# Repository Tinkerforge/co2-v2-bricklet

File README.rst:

CO2 Bricklet 2.0
================

This repository contains the firmware source code and the hardware design
files. The documentation generator configs can be found at
https://github.com/Tinkerforge/generators

Repository Content
------------------

software/:
 * examples/: Examples for all supported languages
 * build/: Compiled files
 * src/: Source code of firmware
 * Makefile: Makefile to build project

hardware/:
 * Contains KiCad project files and additionally schematics as PDF

datasheets/:
 * Contains datasheets for sensors and complex ICs that are used

Hardware
--------

The hardware is designed with the open source EDA Suite KiCad
(http://www.kicad.org). Before you are able to open the files,
you have to install the Tinkerforge kicad-libraries
(https://github.com/Tinkerforge/kicad-libraries). You can either clone
them directly in hardware/ or clone them in a separate folder and
symlink them into hardware/
(ln -s kicad_path/kicad-libraries project_path/hardware). After that you
can open the .pro file in hardware/ with KiCad and from there view and
modify the schematics and the PCB layout.

Software
--------

If you want to do your own Brick/Bricklet firmware development we highly
recommend that you use our build environment setup script and read the
tutorial (https://www.tinkerforge.com/en/doc/Tutorials/Tutorial_Build_Environment/Tutorial.html).

To compile the C code we recommend you to install the newest GNU Arm Embedded
Toolchain (https://launchpad.net/gcc-arm-embedded/+download).
You also need to install bricklib2 (https://github.com/Tinkerforge/bricklib2).

You can either clone it directly in software/src/ or clone it in a
separate folder and symlink it into software/src/
(ln -s bricklib_path/bricklib2 project_path/software/src/). Finally make sure to
have CMake installed (http://www.cmake.org/cmake/resources/software.html).

After that you can build the firmware by invoking make in software/.
The firmware (.zbin) can then be found in software/build/ and uploaded
with brickv (click button "Flashing" on start screen).

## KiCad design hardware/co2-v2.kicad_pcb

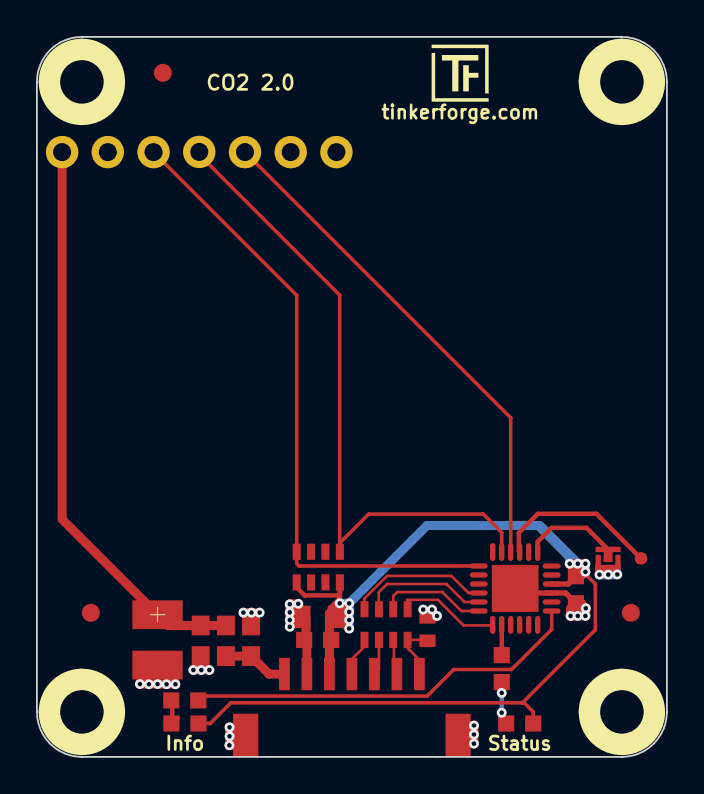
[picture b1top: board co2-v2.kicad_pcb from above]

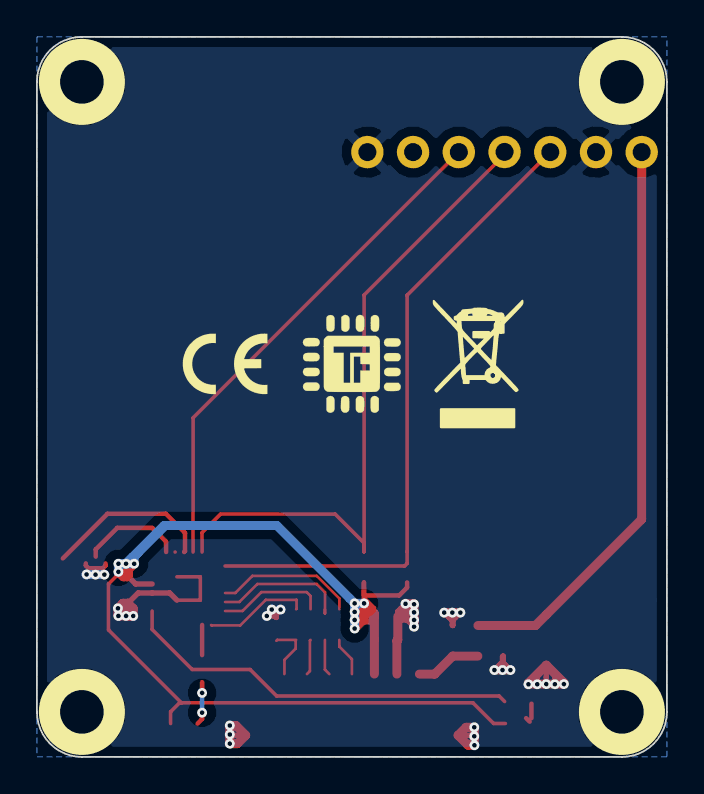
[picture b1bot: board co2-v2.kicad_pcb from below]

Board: 2 copper layers, 35.0 x 40.0 mm, 28 parts (2 on the bottom side), 21 nets.

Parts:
C1: 220pF; C0402E
C2: 10uF; C0805
C3: 1uF; C0603F
C4: 100nF; C0603F
C5, C6: 1µF; C0603E
C7: 100µF; 3528-21
D1: BLUE; D0603F
D2: GREEN; D0603F
Fiducial_Mark: VAL**; Fiducial_Mark
Fiducial_Mark#2, Fiducial_Mark#3: VAL**; Fiducial_Mark
L1: FB-2; R0603E
P1: CON-SENSOR2
P2: DEBUG; DEBUG_PAD
P3: BOOT; SolderJumper
R1, R2: 1k; R0603F
RP1: 82; 4X0603
RP3: 1k; 4X0603
U1: XMC1302; QFN24-4x4mm-0.5mm
U2, U3, U4, U5: DRILL; DRILL_NP
U6: SCD30
VAL: CE_5mm
VAL#2: WEEE_7mm

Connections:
+3.3VP: C2.1, C3.1, C4.1, D1.1, D2.1, P1.3, RP3.5, RP3.8, U1.10
+5V: C5.1, L1.1, P1.1
GND: C1.2, C2.2, C3.2, C4.2, C5.2, C6.2, C7.2, P1.2, P1.EP, P3.1, U1.9, U1.EXP, U6.2, U6.7
unnamed: C1.1, P1.7, RP1.1
unnamed: C6.1, C7.1, L1.2, U6.1
unnamed: D1.2, R1.2
unnamed: D2.2, R2.2
unnamed: P1.4, RP1.4
unnamed: P1.5, RP1.3
unnamed: P1.6, RP1.2
unnamed: P2.1, U1.15
unnamed: P3.2, U1.13
unnamed: R1.1, U1.2
unnamed: R2.1, U1.7
RDY: U1.16, U6.5
S-CLK: RP1.6, U1.23
S-CS: RP1.5, U1.22
S-MISO: RP1.8, U1.1
S-MOSI: RP1.7, U1.24
SCL: RP3.1, U1.19, U6.3
SDA: RP3.4, U1.17, U6.4

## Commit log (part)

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2018-09-04 add readme file and add sensor datasheet
2018-09-04 added kicad project
2018-09-04 added schematics
2018-09-07 added symbol and footprint of the SCD30 to the schematic test if the there are correctly saved to the library
2018-09-10 Update readme to new style
2018-09-10 Add .gitignore
2018-09-17 changed schematic and pcb design
2018-09-18 final pcb prototype design
2018-09-18 added "info" to silkscreen and changed the led positions
2018-09-18 changed led pin and routed new trace on front
2018-09-25 more spi spacing
2019-01-17 fix grid origin, change name
2019-02-15 Add interface description
2019-02-15 Add initial implementation of CO2 V2 firmware
2019-02-18 Only log firmware version if logging level = debug
2019-02-18 Fix air pressure invalid parameter handling
2019-02-18 Fix temperature offset bit shifting
2019-02-18 Add auto-generated examples
2019-02-18 Rename datasheet
2019-02-22 changed processor to XMC1302
2019-03-28 mqtt: Fix whitespace.
2019-03-28 rust: Reformat examples.
2019-04-30 Turn logging off
2019-05-09 add schematic
2019-05-15 fix file names
2019-05-15 add 3d data
2019-05-20 Update auto-generated rust example
2019-05-20 Release Bricklet
2019-05-20 rust: Use merged imports again.
2019-05-29 Increase version for new release (changes in bricklib2)
2019-05-29 Add rev to changelog
2019-08-22 c: Adapt to bindings changes
2019-08-27 go: Escape '%' in examples.
2019-08-28 Improve I2C error handling
    In case of timeout or other error we now completely reconfigure
    the I2C hardware unit and also the SCD30 sensor.
2019-08-28 Correct date and add ref for 2.0.2
2019-12-04 Prefer hPa over mbar
2020-01-13 examples: Use python3 input instead of python2 raw_input.
2020-01-13 examples: mqtt: Remove trailing whitespace.
2020-08-19 Add uc examples.
2020-08-25 uc: Fix whitespace
2020-08-27 uc: Fix warnings.
2020-08-31 uc: Use fixed-with placeholders in format strings.
2020-09-02 uc: Add example driver note.
2020-10-16 uc: Fix divisor type.
2021-10-25 Update KiCad link
    https://www.kicad.org/blog/2021/10/Avoid-links-to-former-kicad-domain/
2022-04-19 Make sure ASC is enabled on each startup
2022-04-19 Add ref for 2.0.3
2022-04-19 examples: uc: Rename TF_HalContext to TF_HAL.
2022-04-27 uc: Adapt to bindings changes
2022-05-10 go: Fix format string
2022-07-06 Add license files.
2025-10-04 Fix compatibility with new Docker build image (GCC 14.2.1)

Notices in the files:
hardware/co2-v2.kicad_pcb:
Licensed under CERN OHL v.1.1
Copyright (©) 2015, T.Schneidermann
